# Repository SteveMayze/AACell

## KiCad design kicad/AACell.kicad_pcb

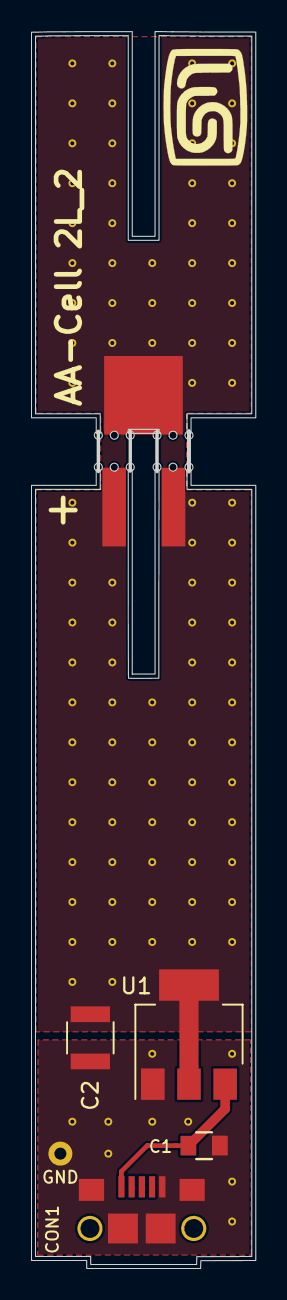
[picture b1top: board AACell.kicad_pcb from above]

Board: 2 copper layers, 14.3 x 78.7 mm, 6 parts (0 on the bottom side), 3 nets.

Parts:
B***: LOGO; AACell-Both
C1: 1μF; C_0805
C2: 1μF; C_1210
CON1: USB-MICRO-B; USB_Micro_B
GND: GND_Connect
U1: ADP3339AKCZ-1.5-R7; SOT-223

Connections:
/VOUT: C2.1, U1.2, U1.4
GND: C1.2, C2.2, CON1.5, CON1.6, CON1.7, CON1.8, CON1.9, GND.1, U1.1
unnamed: C1.1, CON1.1, U1.3

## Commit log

2018-05-06 Initial checkin
2018-05-06 Finished the inial circuit and layout.
    Shortened on of the pieces to avoid the mechanical clash with the
    Micro USB connector.
2018-05-08 Added the SJM logo using the new technique for creating logos
2018-05-16 Adds the PDF for the LDO and redesign of the edge cuts after the feedback from OSH Park
2018-05-19 Adds the gerbers directory to the .gitignore
2018-05-19 Changes the layout and mouse-bites arrangement to ensure + pole pads and 2 layers
2018-05-31 AA-Cell 2L_2 based on the ADP3339AKCZ-1.5-R7 submitted to OSH Park
